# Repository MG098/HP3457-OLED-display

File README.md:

# HP3457-OLED-display
A modern replacement for the low contrast HP3457 Multimeter LCD

This is a remake of the original project made by Xyphro, remade in KiCad and with a simpler PCB.
It drops the complicated power supply structure and isolation, in favor of using internal charge pumps for OLED and a simple buffer chip.
The power is supplied directly through the ribbon cable.
Since the internal ribbon cable follows a DIP-16 dimensions, I decided to use a common DIP socket with pins bent flat to act as a SMD footprint.
This allows for a much simpler and smaller PCB, without the need to split it into two pieces, saving on cost and assembly.
I've also repladced the more uncommon ATMega8L with a very common ATMega328p.
The board is still fully compatibile with ATMega8L, however there are come changes in the code that needed to be made.
Below are the pictures for this simplified board:

# The final result:

I've added a bit of acryllic glass to hide the space between the digits.

# Building the display yourself:

The build procedure is pretty much the same as the original project, but without splitting the board into two pieces.
It uses the same displays as the original project (SSD1316), and I haven't tested it with CH1115 displays.
The original Eagle files are left unchanged and server as a great inspiration.
My modified board is in KiCad folder, and I've also replaced the Gerber files.
If you decide to build this version, make sure that you use an ATMega that was programmed to use an internal oscillator.
I used one that I desoldered from an old arduino, and I couldn't program it before connecting external crystal.
Other fusebits should be set to 8MHz internal oscillator, with no divider.

# Putting it together

Since the display is now a single board, it's thinner than the original and won't fit easily into the multimeter.
For that, I've designed a simple bracket that enables the use of the original mounting holes.
I've included it the 3D folder, along with the 3D model for the board itself.
This bracked is 3D printed and uses brass threaded inserts and M3 screws.
It uses the original mounting holes and screws for the display itself.
After installing, the ribbon cable should fit nicely into the DIP socket and make electrical connection just fine.
The display is using the same 5V provided by the multimeter through the ribbon cable, so there is no need to hook it into AC supply section.
However, 5V into the display is connected through 1K resistor that would need to shorted, otherwise the voltage drop becomes too large.
Shown below is the resistor in question (R615), located right next to the ribbon cable connector.

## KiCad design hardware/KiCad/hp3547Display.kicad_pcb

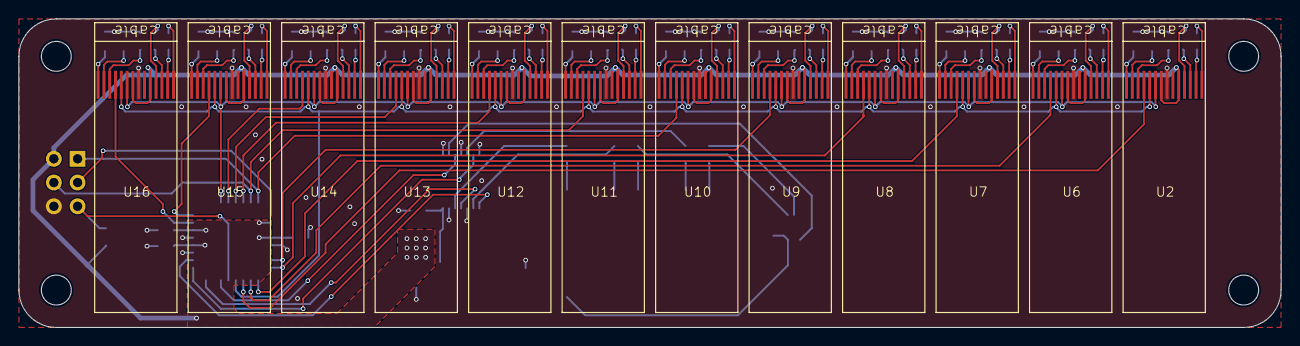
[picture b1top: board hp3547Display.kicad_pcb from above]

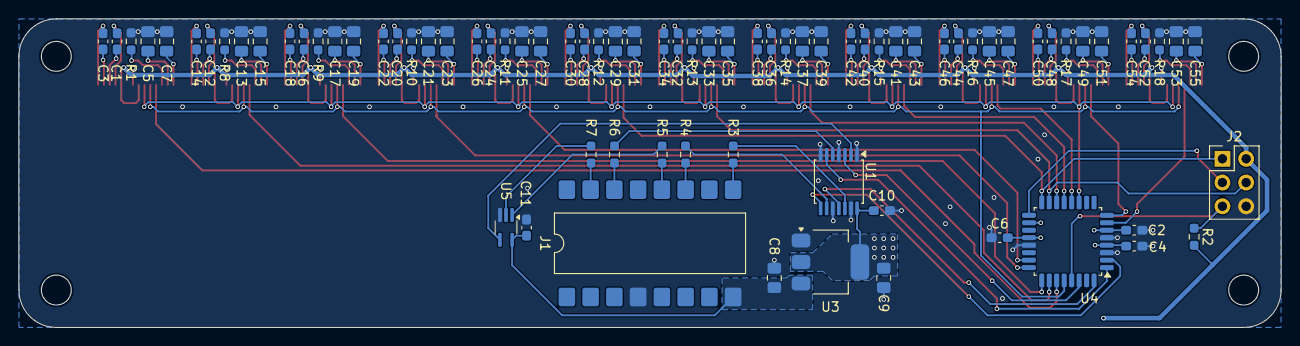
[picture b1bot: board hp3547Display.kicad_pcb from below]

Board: 2 copper layers, 135.0 x 33.0 mm, 95 parts (79 on the bottom side), 118 nets.

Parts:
C1, C2, C3, C4, C6, C10, C11, C12, C14, C16, C18, C20, C22, C24, C26, C28, C30, C32, C34, C36, C38, C40, C42, C44, C46, C48, C50, C52, C54: 1u; C_0603_1608Metric_Pad1.08x0.95mm_HandSolder
C5, C7, C8, C9, C13, C15, C17, C19, C21, C23, C25, C27, C29, C31, C33, C35, C37, C39, C41, C43, C45, C47, C49, C51, C53, C55: 2.2u; C_0805_2012Metric_Pad1.18x1.45mm_HandSolder
H1, H2, H3, H4: M3; MountingHole_3.2mm_M3
J1: HP_DISPLAY_CONN; SMDIP-16_W11.48mm
J2: ICSP; PinHeader_2x03_P2.54mm_Vertical
R1, R8, R9, R10, R11, R12, R13, R14, R15, R16, R17, R18: 560k; R_0603_1608Metric_Pad0.98x0.95mm_HandSolder
R2, R3, R4, R5, R6, R7: 2k; R_0603_1608Metric_Pad0.98x0.95mm_HandSolder
U1: SN74LV4T125; TSSOP-14_4.4x5mm_P0.65mm
U2, U6, U7, U8, U9, U10, U11, U12, U13, U14, U15, U16: OLED_14p; OLED_0.86_14p
U3: AMS1117-3.3; SOT-223-3_TabPin2
U4: ATmega8L-8A; TQFP-32_7x7mm_P0.8mm
U5: 74LVC1G86; SOT-353_SC-70-5_Handsoldering

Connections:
+3.3V: C2.1, C4.1, C6.1, C9.1, C10.1, J2.2, R2.2, U1.14 (VCC), U2.5 (VBAT), U2.8 (VDD), U3.2 (VO), U4.4 (VCC), U4.6 (VCC), U4.18 (AVCC), U4.20 (AREF), U6.5 (VBAT), U6.8 (VDD), U7.5 (VBAT), U7.8 (VDD), U8.5 (VBAT), U8.8 (VDD), U9.5 (VBAT), U9.8 (VDD), U10.5 (VBAT), U10.8 (VDD), U11.5 (VBAT), U11.8 (VDD), U12.5 (VBAT), U12.8 (VDD), U13.5 (VBAT), U13.8 (VDD), U14.5 (VBAT), U14.8 (VDD), U15.5 (VBAT), U15.8 (VDD), U16.5 (VBAT), U16.8 (VDD)
+5V: C8.1, C11.1, J1.8, U3.3 (VI), U5.5 (VCC)
/INA: R5.1, U5.1
/ISA: R7.1, U5.2
/O2: R4.1, U1.9
/PD0: U1.3, U4.30 (PD0)
/PD2: U1.11, U4.32 (PD2)
/PD3: U1.6, U4.1 (PD3)
/PD4: U1.8, U4.2 (PD4)
/PWO: R3.1, U1.12
/RES#: U2.9 (RES#), U4.11 (PD7), U6.9 (RES#), U7.9 (RES#), U8.9 (RES#), U9.9 (RES#), U10.9 (RES#), U11.9 (RES#), U12.9 (RES#), U13.9 (RES#), U14.9 (RES#), U15.9 (RES#), U16.9 (RES#)
/RST: J2.5, R2.1, U4.29 (PC6/~RESET)
/SCK: J2.3, U4.17 (PB5)
/SCL: U2.10 (SCL), U4.28 (PC5), U6.10 (SCL), U7.10 (SCL), U8.10 (SCL), U9.10 (SCL), U10.10 (SCL), U11.10 (SCL), U12.10 (SCL), U13.10 (SCL), U14.10 (SCL), U15.10 (SCL), U16.10 (SCL)
/SDA0: U2.11 (SDA), U4.27 (PC4)
/SDA1: U4.26 (PC3), U6.11 (SDA)
/SDA2: U4.25 (PC2), U7.11 (SDA)
/SDA3: U4.24 (PC1), U8.11 (SDA)
/SDA4: U4.23 (PC0), U9.11 (SDA)
/SDA5: J2.1, U4.16 (PB4), U10.11 (SDA)
/SDA6: J2.4, U4.15 (PB3), U11.11 (SDA)
/SDA7: U4.14 (PB2), U12.11 (SDA)
/SDA8: U4.13 (PB1), U13.11 (SDA)
/SDA9: U4.12 (PB0), U14.11 (SDA)
/SDA10: U4.8 (PB7/XTAL2), U15.11 (SDA)
/SDA11: U4.7 (PB6/XTAL1), U16.11 (SDA)
/SYNC: R6.1, U1.5
GND: C2.2, C4.2, C5.1, C6.2, C7.1, C8.2, C9.2, C10.2, C11.2, C13.1, C15.1, C17.1, C19.1, C21.1, C23.1, C25.1, C27.1, C29.1, C31.1, C33.1, C35.1, C37.1, C39.1, C41.1, C43.1, C45.1, C47.1, C49.1, C51.1, C53.1, C55.1, J1.4, J2.6, R1.2, R8.2, R9.2, R10.2, R11.2, R12.2, R13.2, R14.2, R15.2, R16.2, R17.2, R18.2, U1.1, U1.4, U1.7 (GND), U1.10, U1.13, U2.7 (VSS), U3.1 (GND), U4.3 (GND), U4.5 (GND), U4.21 (AGND), U5.3 (GND), U6.7 (VSS), U7.7 (VSS), U8.7 (VSS), U9.7 (VSS), U10.7 (VSS), U11.7 (VSS), U12.7 (VSS), U13.7 (VSS), U14.7 (VSS), U15.7 (VSS), U16.7 (VSS)
unnamed: J1.9, R3.2
unnamed: J1.11, R4.2
unnamed: J1.12, R5.2
unnamed: J1.14, R6.2
unnamed: J1.15, R7.2
unnamed: U1.2, U5.4
unnamed: C1.1, U2.4 (C1N)
unnamed: C1.2, U2.3 (C1P)
unnamed: C3.1, U2.2 (C2N)
unnamed: C3.2, U2.1 (C2P)
unnamed: R1.1, U2.12 (IREF)
unnamed: C7.2, U2.14 (VCC)
unnamed: C5.2, U2.13 (VCOMH)
unnamed: C12.1, U6.4 (C1N)
unnamed: C12.2, U6.3 (C1P)
unnamed: C14.1, U6.2 (C2N)
unnamed: C14.2, U6.1 (C2P)
unnamed: R8.1, U6.12 (IREF)
unnamed: C15.2, U6.14 (VCC)
unnamed: C13.2, U6.13 (VCOMH)
unnamed: C16.1, U7.4 (C1N)
unnamed: C16.2, U7.3 (C1P)
unnamed: C18.1, U7.2 (C2N)
unnamed: C18.2, U7.1 (C2P)
unnamed: R9.1, U7.12 (IREF)
unnamed: C19.2, U7.14 (VCC)
unnamed: C17.2, U7.13 (VCOMH)
unnamed: C20.1, U8.4 (C1N)
unnamed: C20.2, U8.3 (C1P)
unnamed: C22.1, U8.2 (C2N)
unnamed: C22.2, U8.1 (C2P)
unnamed: R10.1, U8.12 (IREF)
unnamed: C23.2, U8.14 (VCC)
unnamed: C21.2, U8.13 (VCOMH)
unnamed: C24.1, U9.4 (C1N)
unnamed: C24.2, U9.3 (C1P)
unnamed: C26.1, U9.2 (C2N)
unnamed: C26.2, U9.1 (C2P)
unnamed: R11.1, U9.12 (IREF)
unnamed: C27.2, U9.14 (VCC)
unnamed: C25.2, U9.13 (VCOMH)
unnamed: C28.1, U10.4 (C1N)
unnamed: C28.2, U10.3 (C1P)
unnamed: C30.1, U10.2 (C2N)
unnamed: C30.2, U10.1 (C2P)
unnamed: R12.1, U10.12 (IREF)
unnamed: C31.2, U10.14 (VCC)
unnamed: C29.2, U10.13 (VCOMH)
unnamed: C32.1, U11.4 (C1N)
unnamed: C32.2, U11.3 (C1P)
unnamed: C34.1, U11.2 (C2N)
unnamed: C34.2, U11.1 (C2P)
unnamed: R13.1, U11.12 (IREF)
unnamed: C35.2, U11.14 (VCC)
unnamed: C33.2, U11.13 (VCOMH)
unnamed: C36.1, U12.4 (C1N)
unnamed: C36.2, U12.3 (C1P)
unnamed: C38.1, U12.2 (C2N)
unnamed: C38.2, U12.1 (C2P)
unnamed: R14.1, U12.12 (IREF)
unnamed: C39.2, U12.14 (VCC)
unnamed: C37.2, U12.13 (VCOMH)
unnamed: C40.1, U13.4 (C1N)
unnamed: C40.2, U13.3 (C1P)
unnamed: C42.1, U13.2 (C2N)
unnamed: C42.2, U13.1 (C2P)
unnamed: R15.1, U13.12 (IREF)
unnamed: C43.2, U13.14 (VCC)
unnamed: C41.2, U13.13 (VCOMH)
unnamed: C44.1, U14.4 (C1N)
unnamed: C44.2, U14.3 (C1P)
unnamed: C46.1, U14.2 (C2N)
unnamed: C46.2, U14.1 (C2P)
unnamed: R16.1, U14.12 (IREF)
unnamed: C47.2, U14.14 (VCC)
unnamed: C45.2, U14.13 (VCOMH)
unnamed: C48.1, U15.4 (C1N)
unnamed: C48.2, U15.3 (C1P)
unnamed: C50.1, U15.2 (C2N)
unnamed: C50.2, U15.1 (C2P)
unnamed: R17.1, U15.12 (IREF)
unnamed: C51.2, U15.14 (VCC)
unnamed: C49.2, U15.13 (VCOMH)
unnamed: C52.1, U16.4 (C1N)
unnamed: C52.2, U16.3 (C1P)
unnamed: C54.1, U16.2 (C2N)
unnamed: C54.2, U16.1 (C2P)
unnamed: R18.1, U16.12 (IREF)
unnamed: C55.2, U16.14 (VCC)
unnamed: C53.2, U16.13 (VCOMH)

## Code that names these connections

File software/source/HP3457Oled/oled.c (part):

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uint8_t oled_dots [12]; // dot content of all 12 digits

//************************************************************************
// PD7 = RESET
// PC5 = SCL
// PC4, PC3, PC2, PC1, PC0, PC7, PC6 = SDA0..6
// PB2, PB1, PB0, PB7, PB6           = SDA7..11
// PD6 = POWER (high active)
//
// Experimentally determined pixel range:
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
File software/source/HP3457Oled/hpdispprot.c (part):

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
/***********************************************************************
 * Connection scheme:
 * PD0(RXD)    = INA ^ ISA (data) (Actually it would not be required to do a HW XOR, but here it helped to save 
 *                                 money for a 8 line isolator IC. In case you don't want galvanic isolation, you 
 *                                 could optimize the XOR IC away).
 * PD3(INT1)   = SYNC (high = command, low = data)
 * PD4(XCK/T0) = O2 (clock)
 * PD2(INT0)   = PWO (power up)
 **
 * Principle: 
 * The HP3457 sends datagrams that are command + data payload based.
 * The SYNC line identifies if the data is a command (SYNC = HIGH) or data (SYNC = LOW).
 * A command has a bitlength of 10 bits, the data payload is variable in length as function of the received command
 * 
 * PD3 is programmed to generate an interrupt on a rising edge (=start of a command).
 *   Once the interrupt arrives, To will be setup to generate an interrupt for every rising edge of the O2=clock line.
 * This timer interrupt does receive bits and store them for later processing.
 *
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#define	CMD_WRAB1R  (0xda) /* = 0xDA x4 = 0x368 = shift right 1 digit and write registers AB for 1 digit */
#define	CMD_WRABC1L (0xea) /* = 0xEA x4 = 0x3a8 = shift left 1 digit and write registers ABC for 1 digit */
#define	CMD_WRABC1R (0xfa) /* = 0xFA x4 = 0x3e8 = shift left 1 digit and write registers ABC for 1 digit */
#define	CMD_WRITAN  (0xbc) /* = 0xBC x4 = 0x2F0 = write the annunciators (eg the little arrows that are below the digits). The annunciators will follow in the data frame ("INA" line): there is one bit per annunciator, and the top right annunciator is transmitted first */

#define	CMD_DISOFF       (0x8C) /* = 0x8C x4 = 0x230 = Turn display off */
#define	CMD_DISTOG       (0xC8) /* = 0xC8 x4 = 0x320 = toggle the display ON/OFF (I don't know why this command is sent everytime (the sequence is always FC, B8, C8, BC, ...), maybe the unknow command B8 tells to switch the display OFF, then the C8 command swithes the display ON?) */
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
uint8_t cnt=0; // bitcounter for display command receiver

// PD3 interrupt - triggered on every rising edge of the PD3 pin 
ISR(INT1_vect)
{
	if (PIND & (1<<2))
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	PORTD &= ~( (1<<0) | (1<<3) | (1<<4) | (1<<2) ); // all pins = no pullup
	DDRD  &= ~( (1<<0) | (1<<3) | (1<<4) | (1<<2) ); // all pins = input
	
	// Enable rising edge interrupt on PD3 = SYNC
	EICRA |= (1 << ISC11) | (1 << ISC10); // trigger INT1 on rising edge
	EIFR |= (1 << INTF1); // Clear INT1 interrupt flag
	EIMSK |= (1 << INT1); // enable INT1 (It will stay permanently enabled)
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
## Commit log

2026-06-14 Cleanup
